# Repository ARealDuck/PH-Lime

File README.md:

# PH-Lime
A custom made arcade style controller board for the Beatmania IIDX series in double play mode as well as the firmware to support it.

can also be used for Beatmania IIDX SP (single play) mode, the Sound Voltex series games, and even pop'n series games as well. Granted you need supporting firmware for titles outside of Beatmania IIDX titles

I plan on making a wiki detailing everything as well as documentation on how to make your own firmware/modifying current firmware once I get a prototype working.

please do not commercially sell anything or redistribute anything here without my permission first thank you.

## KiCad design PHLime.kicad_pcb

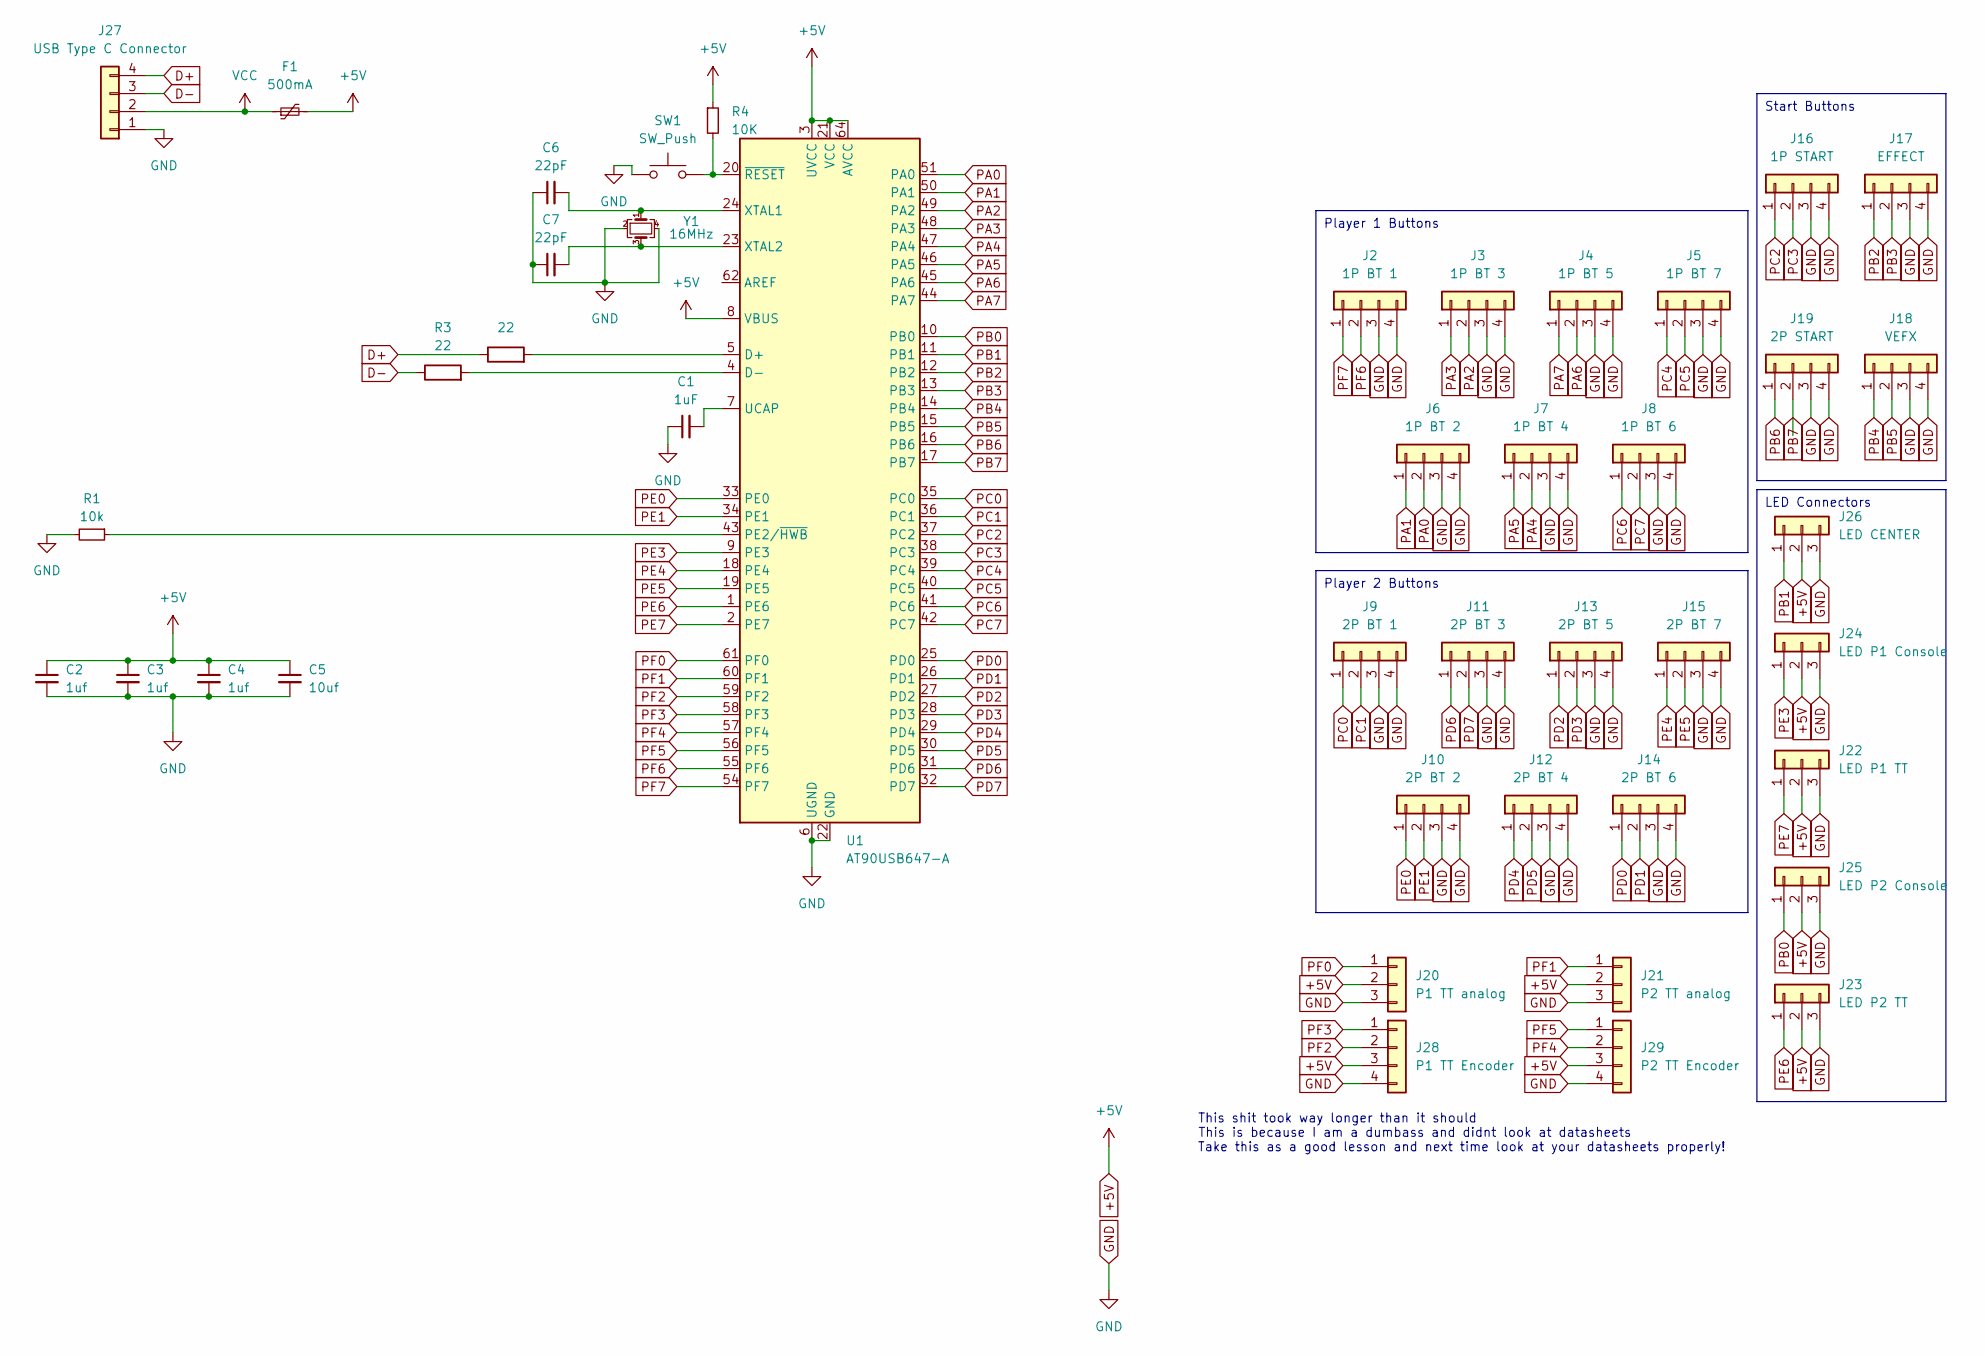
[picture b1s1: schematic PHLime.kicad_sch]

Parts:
C1: 1uF; C_0805_2012Metric
C2, C3, C4: 1uf; C_0805_2012Metric
C5: 10uf; C_0805_2012Metric
C6, C7: 22pF; C_0805_2012Metric
F1: 500mA; Fuse_1206_3216Metric
J2: 1P BT 1; JST_XH_B4B-XH-AM_1x04_P2.50mm_Vertical
J3: 1P BT 3; JST_XH_B4B-XH-AM_1x04_P2.50mm_Vertical
J4: 1P BT 5; JST_XH_B4B-XH-AM_1x04_P2.50mm_Vertical
J5: 1P BT 7; JST_XH_B4B-XH-AM_1x04_P2.50mm_Vertical
J6: 1P BT 2; JST_XH_B4B-XH-AM_1x04_P2.50mm_Vertical
J7: 1P BT 4; JST_XH_B4B-XH-AM_1x04_P2.50mm_Vertical
J8: 1P BT 6; JST_XH_B4B-XH-AM_1x04_P2.50mm_Vertical
J9: 2P BT 1; JST_XH_B4B-XH-AM_1x04_P2.50mm_Vertical
J10: 2P BT 2; JST_XH_B4B-XH-AM_1x04_P2.50mm_Vertical
J11: 2P BT 3; JST_XH_B4B-XH-AM_1x04_P2.50mm_Vertical
J12: 2P BT 4; JST_XH_B4B-XH-AM_1x04_P2.50mm_Vertical
J13: 2P BT 5; JST_XH_B4B-XH-AM_1x04_P2.50mm_Vertical
J14: 2P BT 6; JST_XH_B4B-XH-AM_1x04_P2.50mm_Vertical
J15: 2P BT 7; JST_XH_B4B-XH-AM_1x04_P2.50mm_Vertical
J16: 1P START; JST_XH_B4B-XH-AM_1x04_P2.50mm_Vertical
J17: EFFECT; JST_XH_B4B-XH-AM_1x04_P2.50mm_Vertical
J18: VEFX; JST_XH_B4B-XH-AM_1x04_P2.50mm_Vertical
J19: 2P START; JST_XH_B4B-XH-AM_1x04_P2.50mm_Vertical
J20: P1 TT analog; JST_XH_B3B-XH-AM_1x03_P2.50mm_Vertical
J21: P2 TT analog; JST_XH_B3B-XH-AM_1x03_P2.50mm_Vertical
J22: LED P1 TT; JST_XH_B3B-XH-AM_1x03_P2.50mm_Vertical
J23: LED P2 TT; JST_XH_B3B-XH-AM_1x03_P2.50mm_Vertical
J24: LED P1 Console; JST_XH_B3B-XH-AM_1x03_P2.50mm_Vertical
J25: LED P2 Console; JST_XH_B3B-XH-AM_1x03_P2.50mm_Vertical
J26: LED CENTER; JST_XH_B3B-XH-AM_1x03_P2.50mm_Vertical
J27: USB Type C Connector; JST_XH_B4B-XH-AM_1x04_P2.50mm_Vertical
J28: P1 TT Encoder; JST_XH_B4B-XH-AM_1x04_P2.50mm_Vertical
J29: P2 TT Encoder; JST_XH_B4B-XH-AM_1x04_P2.50mm_Vertical
R1: 10k; R_0805_2012Metric
R2, R3: 22; R_0805_2012Metric
R4: 10K; R_0805_2012Metric
SW1: SW_Push; SW_SPST_SKQG_WithStem
U1: AT90USB647-A; TQFP-64_14x14mm_P0.8mm
Y1: 16MHz; Crystal_SMD_3225-4Pin_3.2x2.5mm

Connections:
+5V: C2.1, C3.1, C4.1, C5.1, F1.2, J20.2, J21.2, J22.2, J23.2, J24.2, J25.2, J26.2, J28.3, J29.3, R4.1, U1.3 (UVCC), U1.8 (VBUS), U1.21 (VCC), U1.52 (VCC), U1.64 (AVCC)
D+: J27.4, R2.1
D-: J27.3, R3.1
GND: C1.1, C2.2, C3.2, C4.2, C5.2, C6.1, C7.1, J2.3, J2.4, J3.3, J3.4, J4.3, J4.4, J5.3, J5.4, J6.3, J6.4, J7.3, J7.4, J8.3, J8.4, J9.3, J9.4, J10.3, J10.4, J11.3, J11.4, J12.3, J12.4, J13.3, J13.4, J14.3, J14.4, J15.3, J15.4, J16.3, J16.4, J17.3, J17.4, J18.3, J18.4, J19.3, J19.4, J20.3, J21.3, J22.3, J23.3, J24.3, J25.3, J26.3, J27.1, J28.4, J29.4, R1.2, SW1.1, U1.6 (UGND), U1.22 (GND), U1.53 (GND), U1.63 (GND), Y1.2, Y1.4
unnamed: R2.2, U1.5 (D+)
unnamed: R3.2, U1.4 (D-)
unnamed: R1.1, U1.43 (PE2/~HWB)
unnamed: C1.2, U1.7 (UCAP)
unnamed: C6.2, U1.24 (XTAL1), Y1.1
unnamed: C7.2, U1.23 (XTAL2), Y1.3
unnamed: R4.2, SW1.2, U1.20 (~RESET)
PA0: J6.2, U1.51 (PA0)
PA1: J6.1, U1.50 (PA1)
PA2: J3.2, U1.49 (PA2)
PA3: J3.1, U1.48 (PA3)
PA4: J7.2, U1.47 (PA4)
PA5: J7.1, U1.46 (PA5)
PA6: J4.2, U1.45 (PA6)
PA7: J4.1, U1.44 (PA7)
PB0: J25.1, U1.10 (PB0)
PB1: J26.1, U1.11 (PB1)
PB2: J17.1, U1.12 (PB2)
PB3: J17.2, U1.13 (PB3)
PB4: J18.1, U1.14 (PB4)
PB5: J18.2, U1.15 (PB5)
PB6: J19.1, U1.16 (PB6)
PB7: J19.2, U1.17 (PB7)
PC0: J9.1, U1.35 (PC0)
PC1: J9.2, U1.36 (PC1)
PC2: J16.1, U1.37 (PC2)
PC3: J16.2, U1.38 (PC3)
PC4: J5.1, U1.39 (PC4)
PC5: J5.2, U1.40 (PC5)
PC6: J8.1, U1.41 (PC6)
PC7: J8.2, U1.42 (PC7)
PD0: J14.1, U1.25 (PD0)
PD1: J14.2, U1.26 (PD1)
PD2: J13.1, U1.27 (PD2)
PD3: J13.2, U1.28 (PD3)
PD4: J12.1, U1.29 (PD4)
PD5: J12.2, U1.30 (PD5)
PD6: J11.1, U1.31 (PD6)
PD7: J11.2, U1.32 (PD7)
PE0: J10.1, U1.33 (PE0)
PE1: J10.2, U1.34 (PE1)
PE3: J24.1, U1.9 (PE3)
PE4: J15.1, U1.18 (PE4)
PE5: J15.2, U1.19 (PE5)
PE6: J23.1, U1.1 (PE6)
PE7: J22.1, U1.2 (PE7)
PF0: J20.1, U1.61 (PF0)
PF1: J21.1, U1.60 (PF1)
PF2: J28.2, U1.59 (PF2)
PF3: J28.1, U1.58 (PF3)
PF4: J29.2, U1.57 (PF4)
PF5: J29.1, U1.56 (PF5)
PF6: J2.2, U1.55 (PF6)
PF7: J2.1, U1.54 (PF7)
VCC: F1.1, J27.2

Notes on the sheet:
Player 1 Buttons
Player 2 Buttons
Start Buttons
LED Connectors
This is because I am a dumbass and didnt look at datasheets
Take this as a good lesson and next time look at your datasheets properly!
This shit took way longer than it should

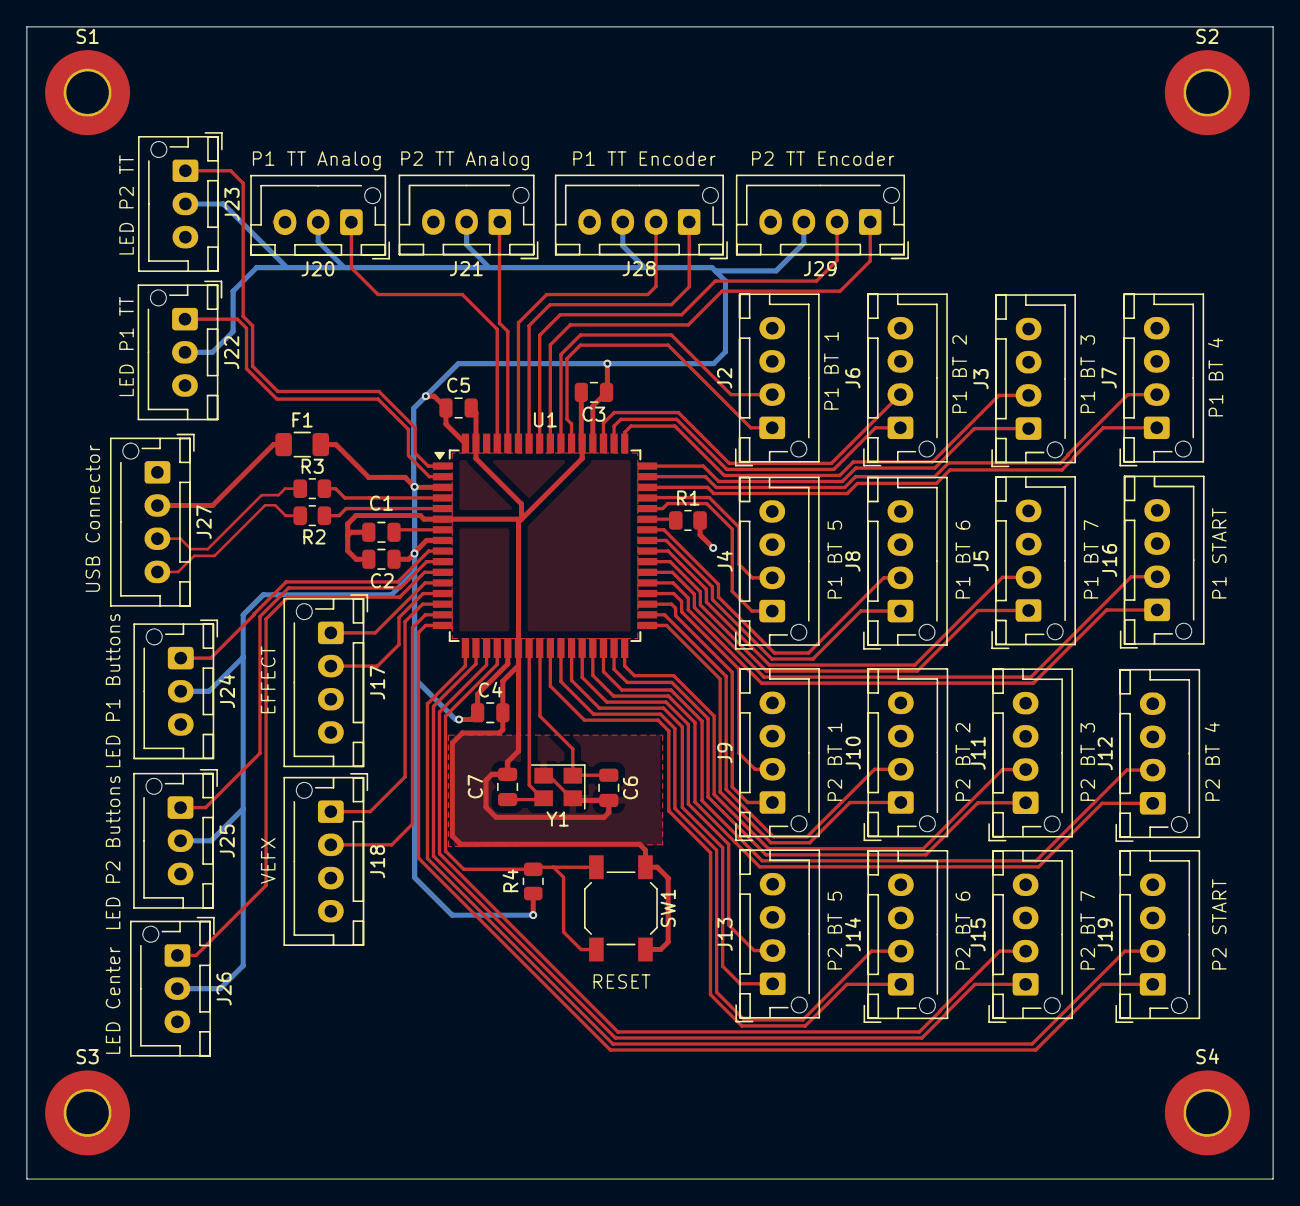
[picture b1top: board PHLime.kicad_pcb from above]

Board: 2 copper layers, 93.9 x 86.8 mm, 47 parts (0 on the bottom side), 59 nets.

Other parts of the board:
S1, S2, S3, S4: MountingHole_3.2mm_M3_Pad_TopBottom

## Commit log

2024-04-06 add current files to project
2024-04-06 added submodules
2024-04-06 symbol VOMIT
    updated footprints and started PCB work lol
2024-04-07 attempt at compacting connectors
2024-04-11 Schematic rewrite maybe?
2024-04-12 Reworking stuffs
    reworking schematic whilst tracing the PCB at the same time how fun!!!!
2024-04-13 I forgot to commit this oopsiedaisies
2024-04-14 AAAAAAAA
2024-04-14 I should finally get to doing this
2024-04-14 Your Honor, League of Legends.
2024-04-14 Death.
2024-04-14 Dumb
2024-04-14 Delete ~PHIIDXDP.kicad_sch.lck
    More Dumb
2024-04-14 Even More Dumb
2024-04-14 Who Woulda guessed? More Dumb!
2024-04-15 Wha?
2024-04-16 No way!
2024-04-16 Renaming Files
2024-04-19 Changes, somehow?
2024-04-25 Mounting Holes
2024-04-25 Ground Planes OP
2024-04-26 Wow I feel really dumb for not doing this.
